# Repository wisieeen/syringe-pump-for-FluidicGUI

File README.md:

# Infusion Pump Project

An open-source, DIY infusion pump system designed for precision fluid handling in chemistry and laboratory applications.

## Overview

This repository contains all the necessary components to build your own programmable infusion pump system, including 3D models for printing the mechanical components, PCB designs for the electronics, and firmware for controlling the system.

## Repository Structure

- **3d_models/** - 3D printable files for the physical components
  - **pump/** - Main pump components
  - **tube_connectors/** - Components for fluid connections

- **electronics/** - PCB designs and schematic files
  - **power_distribution_board/** - Power supply and distribution circuits
  - **pump_main_board/** - Main control board for the pump

- **firmware/** - Software that runs on the pump hardware
  - **syringe_pump_master/** - Controller firmware for the pump system

## Features

- Precision fluid control
- Programmable flow rates
- Compatible with standard syringes and tubing
- Modular design for easy customization
- Open-source hardware and software

## Getting Started

### Hardware Requirements

- 3D printer for fabricating components, I use and recommend PETG material
- Electronic components: Seeed Studio Xiao ESP32C3, TMC2209 module, 1Kohm resistors (THT or 0805 SMD), LED, 4p 2.54mm JST connector, 6p 2.54mm JST connector, 7p pin sockets, 8p pin sockets, 12mm M3 screws, 16mm M3 screws, M3 nuts, m3 washers
- Tools for assembly: Screwdriver, soldering iron, solder
- Wifi network

### Building the Pump

1. Print the 3D models from the `3d_models` directory
2. Manufacture PCBs using files in the `electronics` directory
3. Assemble the hardware components
4. Flash the firmware to the microcontroller

### Software Setup

Use Arduino IDE to upload firmware to microcontroller Seeed Studio Xiao ESP32C3. Make sure to set mqtt_server IP, unique device_name, WiFiClient and PubSubClient client (set in syringe_pump_master.ino)

## License

This project is open-source and available under the MIT License.

## Contributing

Contributions to improve the design, firmware, or documentation are welcome. Please feel free to submit pull requests or open issues for discussion.

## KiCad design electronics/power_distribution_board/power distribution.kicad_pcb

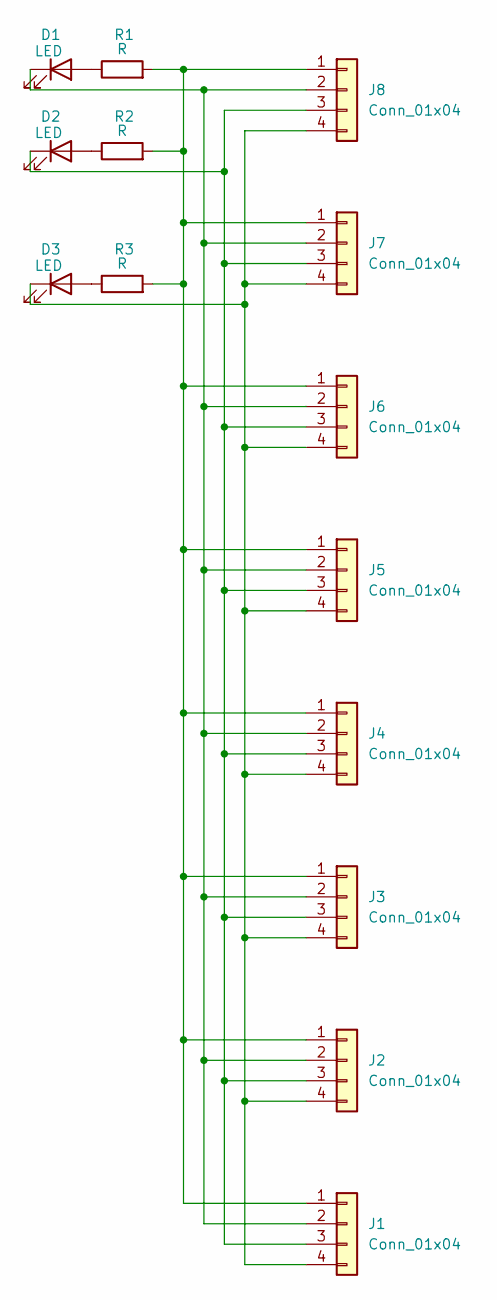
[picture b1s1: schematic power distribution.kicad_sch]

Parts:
D1, D2, D3: LED; LED_0805_2012Metric
J1, J2, J3, J4, J5, J6, J7, J8: Conn_01x04; JST_EH_B4B-EH-A_1x04_P2.50mm_Vertical
R1, R2, R3: R; R_0805_2012Metric

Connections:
unnamed: D1.2 (A), R1.1
unnamed: D1.1 (K), J1.2, J2.2, J3.2, J4.2, J5.2, J6.2, J7.2, J8.2
unnamed: D2.2 (A), R2.1
unnamed: D2.1 (K), J1.3, J2.3, J3.3, J4.3, J5.3, J6.3, J7.3, J8.3
unnamed: D3.2 (A), R3.1
unnamed: D3.1 (K), J1.4, J2.4, J3.4, J4.4, J5.4, J6.4, J7.4, J8.4
unnamed: J1.1, J2.1, J3.1, J4.1, J5.1, J6.1, J7.1, J8.1, R1.2, R2.2, R3.2

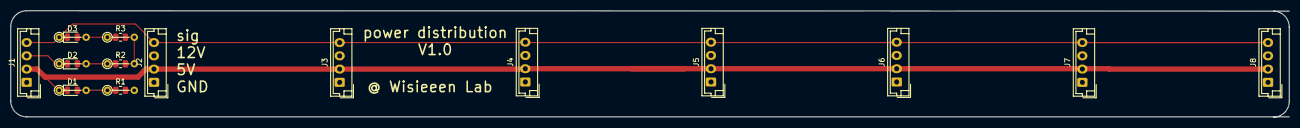
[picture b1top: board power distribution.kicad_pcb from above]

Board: 2 copper layers, 241.0 x 20.1 mm, 14 parts (0 on the bottom side), 7 nets.

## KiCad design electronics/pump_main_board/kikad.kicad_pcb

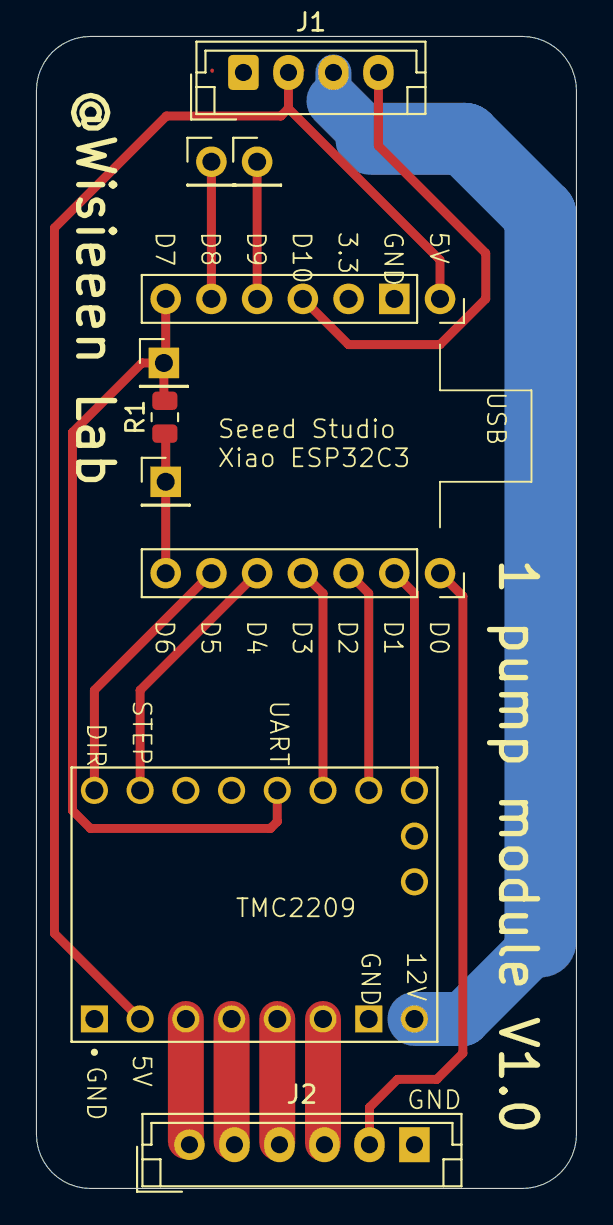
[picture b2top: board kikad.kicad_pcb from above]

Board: 2 copper layers, 30.0 x 64.0 mm, 5 parts (0 on the bottom side), 14 nets.

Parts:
J1: Conn_01x04_Socket; JST_EH_B4B-EH-A_1x04_P2.50mm_Vertical
J2: Conn_01x06_Socket; JST_EH_B6B-EH-A_1x06_P2.50mm_Vertical
R1: 1k; R_0805_2012Metric
U1: TMC2209_SILENTSTEPSTICK; MODULE_TMC2209_SILENTSTEPSTICK
U2: MOUDLE-SEEEDUINO-XIAO-ESP32C3; 2.54_socket_for_xiao_esp32

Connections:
+5V: J1.2, U1.2 (VIO), U2.13 (GND)
+12V: J1.3, U1.8 (VM)
GND: J1.1, J2.6, U1.1 (GND), U1.7 (GND), U2.12 (3V3)
unnamed: J1.4, U2.10 (PA5_A9_D9_MISO)
unnamed: J2.1, U1.3 (M1B)
unnamed: J2.2, U1.4 (M1A)
unnamed: J2.3, U1.5 (M2A)
unnamed: J2.4, U1.6 (M2B)
unnamed: J2.5, U2.0
unnamed: U1.9 (DIR), U2.5 (PA8_A4_D4_SDA)
unnamed: R1.2, U1.13 (SPRD), U2.7 (PB08_A6_D6_TX)
unnamed: U1.10 (STEP), U2.4 (PA11_A3_D3)
unnamed: U1.16 (~EN), U2.1 (PA02_A0_D0)
unnamed: R1.1, U2.6 (PA9_A5_D5_SCL)

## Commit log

2025-03-06 Initial commit of pump files
2025-04-06 3D model update
    3D models dimensions were optimised to save space in assembly, printing time and material
2025-04-12 3d model optimization and PCB
    3d model:
    - decreased material use
    - reduced overall width, increased depth
    - modified screw slots for precision and stress management
    PCB:
    - created PCB for power and signal distribution
2025-04-12 readme added
